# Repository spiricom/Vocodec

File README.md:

# Vocodec repository
Repository of code for the Snyderphonics Vocodec vocal processor unit.
requires LEAF as a submodule.

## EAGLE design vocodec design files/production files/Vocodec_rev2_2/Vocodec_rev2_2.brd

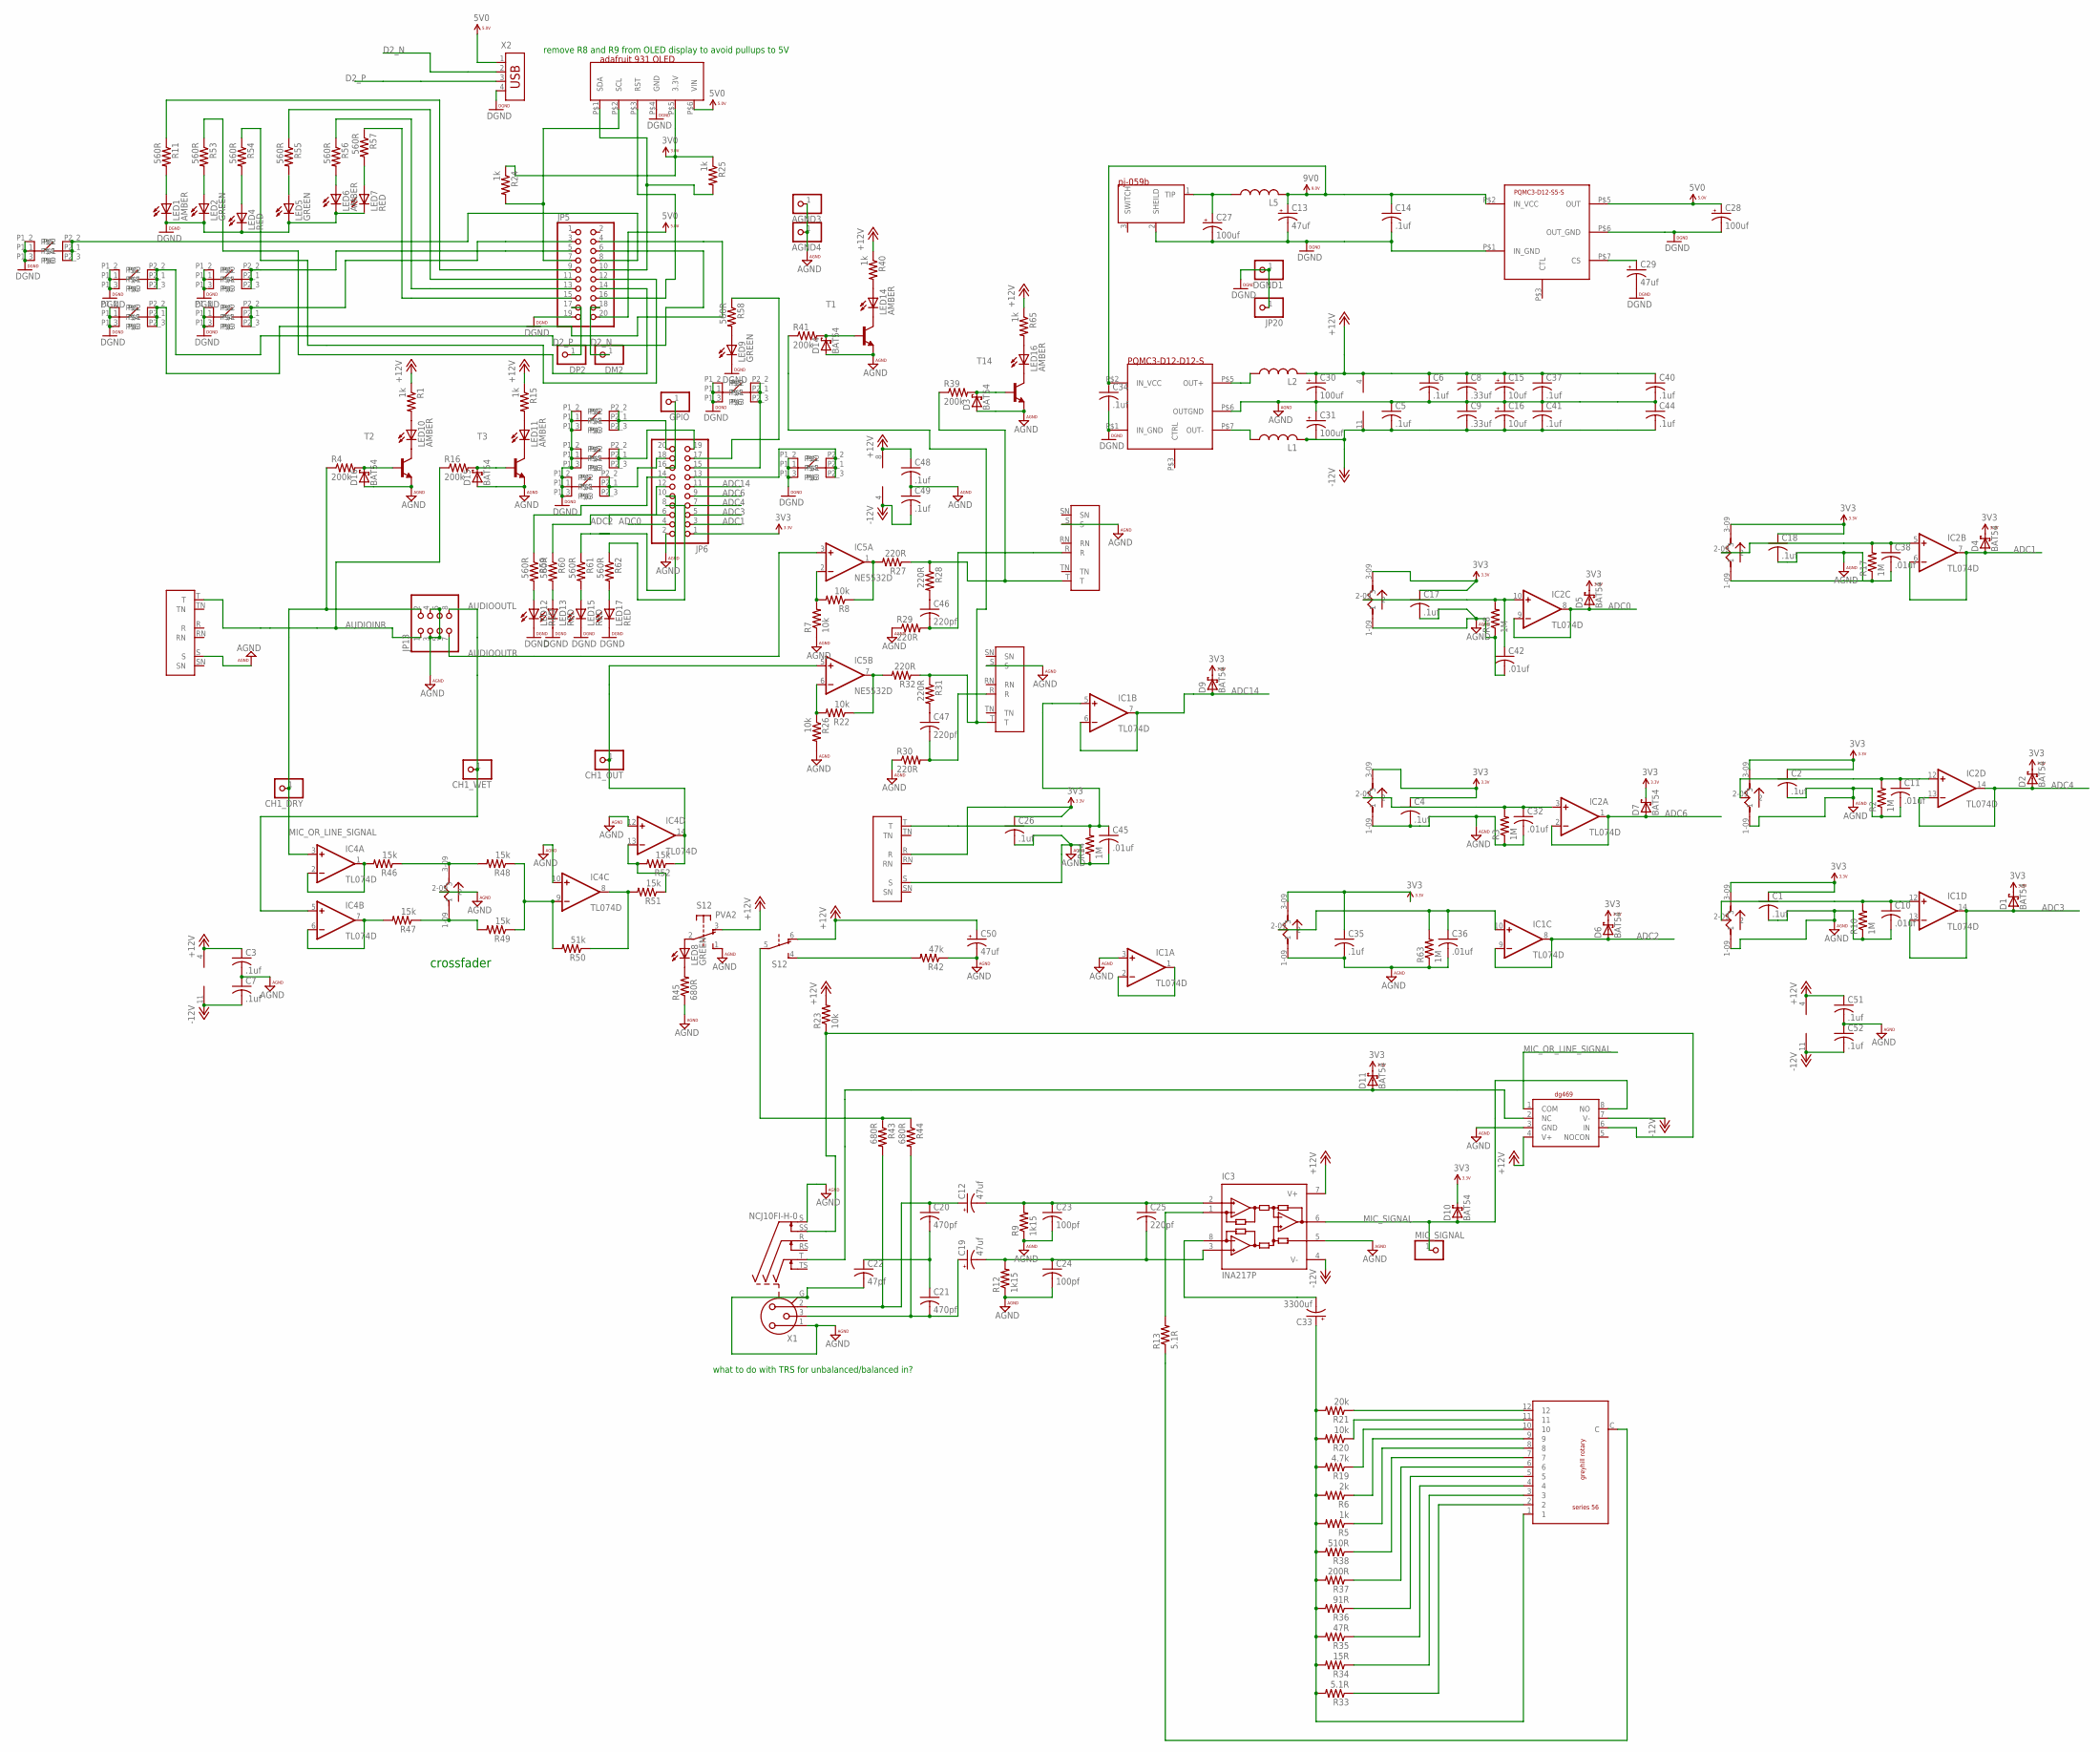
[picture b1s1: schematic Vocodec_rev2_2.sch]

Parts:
AGND3, AGND4: PINHD-1X1; 1X01; PARTNO *DNP
C1, C2, C3, C4, C5, C6, C7, C14, C17, C18, C26, C34, C35, C37, C40, C41, C44, C48, C49, C51, C52: .1uf; C0603; PARTNO CC0603KRX7R8BB104
C8, C9: .33uf; C0603; PARTNO C1608X7R1H334K080AC
C10, C11, C32, C36, C38, C42, C45: .01uf; C0603; PARTNO CC0603KRX7R8BB103
C12, C13, C19, C29, C50: 47uf; PANASONIC_E; PARTNO EEE-1VA470AP
C15, C16: 10uf; PANASONIC_C; PARTNO EEE-1VA100AR
C20, C21: 470pf; C0603; PARTNO CC0603JRNPO9BN471
C22: 47pf; C0603; PARTNO C0603C470J5GACTU
C23, C24: 100pf; C0603; PARTNO C0603C101J3GACTU
C25, C46, C47: 220pf; C0603; PARTNO CC0603JRNPO9BN221
C27, C28, C30, C31: 100uf; PANASONIC_F; PARTNO EEE-1EA101P
C33: 3300uf; E5-13; PARTNO EEU-FR1A332
CH1_DRY, CH1_OUT, CH1_WET: PINHD-1X1; 1X01; PARTNO *DNP
D1, D2, D3, D4, D5, D6, D7, D9, D10, D11, D14, D15, D16: BAT54; SOT23; PARTNO BAT54
DGND1: PINHD-1X1; 1X01; PARTNO *DNP
DM2: PINHD-1X1; 1X01; PARTNO *DNP
DP2: PINHD-1X1; 1X01; PARTNO *DNP
GPIO: PINHD-1X1; 1X01; PARTNO *DNP
IC1, IC2, IC4: TL074D; SO14; PARTNO TL074CDR
IC3: INA217P; DIL08; PARTNO *DNP
IC5: NE5532D; SO08; PARTNO NE5532DR
IC11: PQMC3-D12-D12-S; PARTNO PQMC3-D12-D12-S
IC12: PQMC3-D12-S5-S; PQMC3-D12-D12-S; PARTNO PQMC3-D12-S5-S
IC13: DG469; SO8; PARTNO DG469EY-T1-E3
J1, J3, J4, J9: NRJ6HF2; PARTNO NRJ6HF
J10: PJ-059B; PARTNO PJ-059A
JP5, JP6: PINHD-2X10; 2X10; PARTNO PRPC010DAAN-RC
JP13: PINHD-2X4; 2X04; PARTNO PRPC004DAAN-RC
JP20: PINHD-1X1; 1X01; PARTNO *DNP
L1, L2, L5: L-US6000-XXX-RC; 6000-XXXX-RC; PARTNO RLB9012-100KL
LED1, LED6, LED10, LED11, LED14, LED16: AMBER; PLCC2; PARTNO HSMU-A100-S00J1
LED2, LED5, LED8, LED9: GREEN; PLCC2; PARTNO HSMM-A101-R00J1
LED4, LED7, LED12, LED13, LED15, LED17: RED; PLCC2; PARTNO HSMZ-A100-R00J1
MIC_SIGNAL: PINHD-1X1; 1X01; PARTNO *DNP
OLED1: ADAFRUIT_931_OLED_128X32; ADAFRUIT_128X32_OLED; PARTNO *DNP
R1, R5, R15, R24, R25, R40, R65: 1k; R0603; PARTNO ESR03EZPF1001
R2, R3, R10, R14, R17, R18, R63: 1M; R0603; PARTNO CRCW06031M00FKEAHP
R4, R16, R39, R41: 200k; R0603; PARTNO ESR03EZPJ204
R6: 2k; R0603; PARTNO ERJ-PA3F2001V
R7, R8, R20, R22, R23, R26: 10k; R0603; PARTNO ESR03EZPF1002
R9, R12: 1k15; R0603; PARTNO ERA-3AEB1151V
R11, R53, R54, R55, R56, R57, R58, R59, R60, R61, R62: 560R; R0603; PARTNO ESR03EZPF5600
R13, R33: 5.1R; R0603; PARTNO RC0603JR-075R1L
R19: 4.7k; R0603; PARTNO CRCW06034K70FKEAHP
R21: 20k; R0603; PARTNO ESR03EZPF2002
R27, R28, R29, R30, R31, R32: 220R; R0603; PARTNO ESR03EZPJ221
R34: 15R; R0603; PARTNO RC0603JR-0715RL
R35: 47R; R0603; PARTNO RC0603JR-0747RL
R36: 91R; R0603; PARTNO RC0603JR-0791RL
R37: 200R; R0603; PARTNO RC0603JR-07200RL
R38: 510R; R0603; PARTNO RC0603JR-07510RL
R42: 47k; R0603; PARTNO ESR03EZPJ473
R43, R44, R45: 680R; R0603; PARTNO CRCW0603680RJNEAHP
R46, R47, R48, R49, R51, R52: 15k; R0603; PARTNO ESR03EZPF1502
R50: 51k; R0603; PARTNO ERJ-PA3F5102V
S12: PVA2; PVA2F; PARTNO PVA2 OA H4 1.7N V2
T1, T2, T3, T14: MMBT3904LT1-NPN-SOT23-BEC; SOT23-BEC; PARTNO MMBT3904-TP
U$1: 56DP30; PARTNO 56DP30-01-1-AJN
U$7, U$11, U$33, U$39, U$40, U$42, U$43, U$44, U$45, U$48: TL52_PLUS; PARTNO *DNP
U$12, U$14, U$16, U$27, U$28, U$31, U$32: RK09; PARTNO *DNP
X1: NCJ10FI-H-0; PARTNO NCJ10FI-H-01
X2: USB-787616; USB; PARTNO 292303-1

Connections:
3V0: OLED1.P$5 (3.3V), R24.1, R25.1
3V3: C1.1, C2.1, C4.1, C17.1, C18.1, C26.1, C35.1, D1.3 (C), D2.3 (C), D4.3 (C), D5.3 (C), D6.3 (C), D7.3 (C), D9.3 (C), D10.3 (C), D11.3 (C), J9.R, JP6.1, U$12.3-09 (3), U$16.3-09 (3), U$27.3-09 (3), U$28.3-09 (3), U$31.3-09 (3), U$32.3-09 (3)
5V0: C28.+, IC12.P$5 (OUT), JP5.20, OLED1.P$6 (VIN), X2.1
9V0: C13.+, C14.1, C34.1, IC11.P$2 (IN_VCC), IC12.P$2 (IN_VCC), L5.2
+12V: C3.1, C6.1, C8.1, C15.+, C30.+, C37.1, C40.1, C48.1, C50.+, C51.1, IC1.4 (V+), IC2.4 (V+), IC3.7 (V+), IC4.4 (V+), IC5.8 (V+), IC13.4 (V+), L2.2, R1.1, R15.1, R23.2, R40.1, R65.1, S12.3 (O), S12.6 (O)
-12V: C5.2, C7.2, C9.2, C16.-, C31.-, C41.2, C44.2, C49.2, C52.2, IC1.11 (V-), IC2.11 (V-), IC3.4 (V-), IC4.11 (V-), IC5.4 (V-), IC13.7 (V-), L1.2
ADC0: D5.1 (A), IC2.8 (OUT), IC2.9 (-IN), JP6.4
ADC1: D4.1 (A), IC2.6 (-IN), IC2.7 (OUT), JP6.3
ADC2: D6.1 (A), IC1.8 (OUT), IC1.9 (-IN), JP6.6
ADC3: D1.1 (A), IC1.13 (-IN), IC1.14 (OUT), JP6.5
ADC4: D2.1 (A), IC2.13 (-IN), IC2.14 (OUT), JP6.7
ADC6: D7.1 (A), IC2.1 (OUT), IC2.2 (-IN), JP6.9
ADC14: D9.1 (A), IC1.6 (-IN), IC1.7 (OUT), JP6.11
AGND: AGND3.1, AGND4.1, C1.2, C2.2, C3.2, C4.2, C5.1, C6.2, C7.1, C8.2, C9.1, C10.2, C11.2, C15.-, C16.+, C17.2, C18.2, C22.2, C23.2, C24.2, C26.2, C30.-, C31.+, C32.2, C35.2, C36.2, C37.2, C38.2, C40.2, C41.1, C42.2, C44.1, C45.2, C48.2, C49.1, C50.-, C51.2, C52.1, D3.1 (A), D14.1 (A), D15.1 (A), D16.1 (A), IC1.3 (+IN), IC3.5 (REF), IC4.10 (+IN), IC4.12 (+IN), IC11.P$6 (OUTGND), IC13.3 (GND), J1.S, J3.S, J4.S, J9.S, JP6.2, JP13.3, JP13.4, JP13.5, JP13.6, R2.1, R3.1, R7.1, R9.1, R10.1, R12.1, R14.1, R17.1, R18.1, R26.2, R29.1, R30.1, R42.1, R45.1, R63.1, S12.1 (S), T1.E, T2.E, T3.E, T14.E, U$12.1-09 (1), U$14.2-09 (2), U$16.1-09 (1), U$27.1-09 (1), U$28.1-09 (1), U$31.1-09 (1), U$32.1-09 (1), X1.1, X1.G, X1.S
AUDIOINR: J1.T, JP13.1, R16.1
AUDIOOUTL: CH1_WET.1, IC4.5 (+IN), JP13.8
AUDIOOUTR: IC5.3 (+IN), JP13.7
D2_N: DM2.1, JP5.18, X2.2
D2_P: DP2.1, JP5.17, X2.3
DGND: C13.-, C14.2, C27.-, C28.-, C29.-, C34.2, DGND1.1, IC11.P$1 (IN_GND), IC12.P$1 (IN_GND), IC12.P$6 (OUT_GND), J10.2 (SHEILD), JP5.19, JP20.1, LED1.C, LED2.C, LED4.C, LED5.C, LED6.C, LED7.C, LED9.C, LED12.C, LED13.C, LED15.C, LED17.C, OLED1.P$4 (GND), U$7.P1_1, U$7.P1_2, U$7.P1_3, U$11.P1_1, U$11.P1_2, U$11.P1_3, U$33.P1_1, U$33.P1_2, U$33.P1_3, U$39.P1_1, U$39.P1_2, U$39.P1_3, U$40.P1_1, U$40.P1_2, U$40.P1_3, U$42.P1_1, U$42.P1_2, U$42.P1_3, U$43.P1_1, U$43.P1_2, U$43.P1_3, U$44.P1_1, U$44.P1_2, U$44.P1_3, U$45.P1_1, U$45.P1_2, U$45.P1_3, U$48.P1_1, U$48.P1_2, U$48.P1_3, X2.4
MIC_OR_LINE_SIGNAL: CH1_DRY.1, IC4.3 (+IN), IC13.1 (COM), JP13.2, R4.1
MIC_SIGNAL: D10.1 (A), IC3.6 (OUT), IC13.8 (NO), MIC_SIGNAL.1
unnamed: IC5.2 (-IN), R7.2, R8.2
unnamed: IC5.6 (-IN), R22.2, R26.1
unnamed: LED10.C, T2.C
unnamed: IC5.1 (OUT), R8.1, R27.2
unnamed: LED10.A, R1.2
unnamed: IC1.1 (OUT), IC1.2 (-IN)
unnamed: LED11.C, T3.C
unnamed: D16.3 (C), R4.2, T2.B
unnamed: IC5.7 (OUT), R22.1, R32.2
unnamed: IC13.6 (IN), R23.1, X1.SS
unnamed: LED11.A, R15.2
unnamed: C33.+, R5.2, R6.2, R19.2, R20.2, R21.2, R33.2, R34.2, R35.2, R36.2, R37.2, R38.2, U$1.1
unnamed: D15.3 (C), R16.2, T3.B
unnamed: IC11.P$5 (OUT+), L2.1
unnamed: IC11.P$7 (OUT-), L1.1
unnamed: LED14.C, T1.C
unnamed: LED14.A, R40.2
unnamed: JP6.19, U$45.P2_1, U$45.P2_2, U$45.P2_3
unnamed: R21.1, U$1.12
unnamed: R20.1, U$1.11
unnamed: C12.-, C23.1, C25.1, IC3.2 (-IN), R9.2
unnamed: C19.+, C21.2, R44.2, X1.3
unnamed: C12.+, C20.1, R43.2, X1.2
unnamed: C20.2, C21.1, C22.1
unnamed: LED16.C, T14.C
unnamed: LED16.A, R65.2
unnamed: R19.1, U$1.10
unnamed: R6.1, U$1.9
unnamed: C19.-, C24.1, C25.2, IC3.3 (+IN), R12.2
unnamed: LED8.A, S12.2
unnamed: IC3.1 (RG1), R13.2
unnamed: D11.1 (A), IC13.2 (NC), X1.T
unnamed: R5.1, U$1.8
unnamed: R38.1, U$1.7
unnamed: R13.1, U$1.C
unnamed: R37.1, U$1.6
unnamed: R36.1, U$1.5
unnamed: R35.1, U$1.4
unnamed: R34.1, U$1.3
unnamed: R33.1, U$1.2
unnamed: J3.T, R27.1, R28.1, R39.1
unnamed: C46.2, J3.R, R29.2
unnamed: R42.2, S12.4 (S)
unnamed: C47.2, J4.R, R30.2
unnamed: D3.3 (C), R39.2, T14.B
unnamed: C46.1, R28.2
unnamed: C47.1, R31.2
unnamed: J4.T, R31.1, R32.1, R41.1
unnamed: LED8.C, R45.2
unnamed: C27.+, J10.1 (TIP), L5.1
unnamed: IC4.1 (OUT), IC4.2 (-IN), R46.2
unnamed: D14.3 (C), R41.2, T1.B
unnamed: C29.+, IC12.P$7 (CS)
unnamed: R43.1, R44.1, S12.5
unnamed: IC4.6 (-IN), IC4.7 (OUT), R47.2
unnamed: R46.1, R48.2, U$14.3-09 (3)
unnamed: C36.1, IC1.10 (+IN), R63.2, U$16.2-09 (2)
unnamed: IC4.8 (OUT), R50.1, R51.2
unnamed: IC4.9 (-IN), R48.1, R49.1, R50.2
unnamed: IC4.13 (-IN), R51.1, R52.2
unnamed: LED1.A, R11.2
unnamed: LED2.A, R53.2
unnamed: CH1_OUT.1, IC4.14 (OUT), IC5.5 (+IN), R52.1
unnamed: LED4.A, R54.2
unnamed: LED5.A, R55.2
unnamed: JP6.18, U$48.P2_1, U$48.P2_2, U$48.P2_3
unnamed: C33.-, IC3.8 (RG2)
unnamed: LED9.A, R58.2
unnamed: JP6.17, R58.1
unnamed: LED6.A, R56.2
unnamed: LED7.A, R57.2
unnamed: JP6.15, U$43.P2_1, U$43.P2_2, U$43.P2_3
unnamed: JP6.13, U$42.P2_1, U$42.P2_2, U$42.P2_3
unnamed: LED12.A, R59.2
unnamed: LED13.A, R60.2
unnamed: JP6.20, U$44.P2_1, U$44.P2_2, U$44.P2_3
unnamed: LED15.A, R61.2
unnamed: LED17.A, R62.2
unnamed: JP6.14, R59.1
unnamed: JP6.12, R60.1
unnamed: JP6.10, R61.1
unnamed: JP6.8, R62.1
unnamed: GPIO.1, JP6.16
unnamed: R47.1, R49.2, U$14.1-09 (1)
PA8: JP5.13, R56.1
PA9: JP5.16, OLED1.P$3 (RST)
PA10: JP5.15, R57.1
PB12: JP5.4, U$39.P2_1, U$39.P2_2, U$39.P2_3
PB13: JP5.3, U$7.P2_1, U$7.P2_2, U$7.P2_3
PB14: JP5.6, U$33.P2_1, U$33.P2_2, U$33.P2_3
PB15: JP5.5, U$11.P2_1, U$11.P2_2, U$11.P2_3
PC6: JP5.9, R11.1
PC7: JP5.12, R54.1
PC8: JP5.11, R55.1
PC9: JP5.14, R53.1
PD11_NOTIMER: JP5.8, U$40.P2_1, U$40.P2_2, U$40.P2_3
POT1: C10.1, IC1.12 (+IN), R10.2, U$12.2-09 (2)
POT3: C32.1, IC2.3 (+IN), R3.2, U$32.2-09 (2)
POT4: C11.1, IC2.12 (+IN), R2.2, U$31.2-09 (2)
POT7: C38.1, IC2.5 (+IN), R17.2, U$28.2-09 (2)
POT8: C42.1, IC2.10 (+IN), R18.2, U$27.2-09 (2)
POT9: C45.1, IC1.5 (+IN), J9.T, R14.2
SCL: JP5.7, OLED1.P$2 (SCL), R24.2
SDA: JP5.10, OLED1.P$1 (SDA), R25.2

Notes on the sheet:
remove R8 and R9 from OLED display to avoid pullups to 5V
crossfader
what to do with TRS for unbalanced/balanced in?

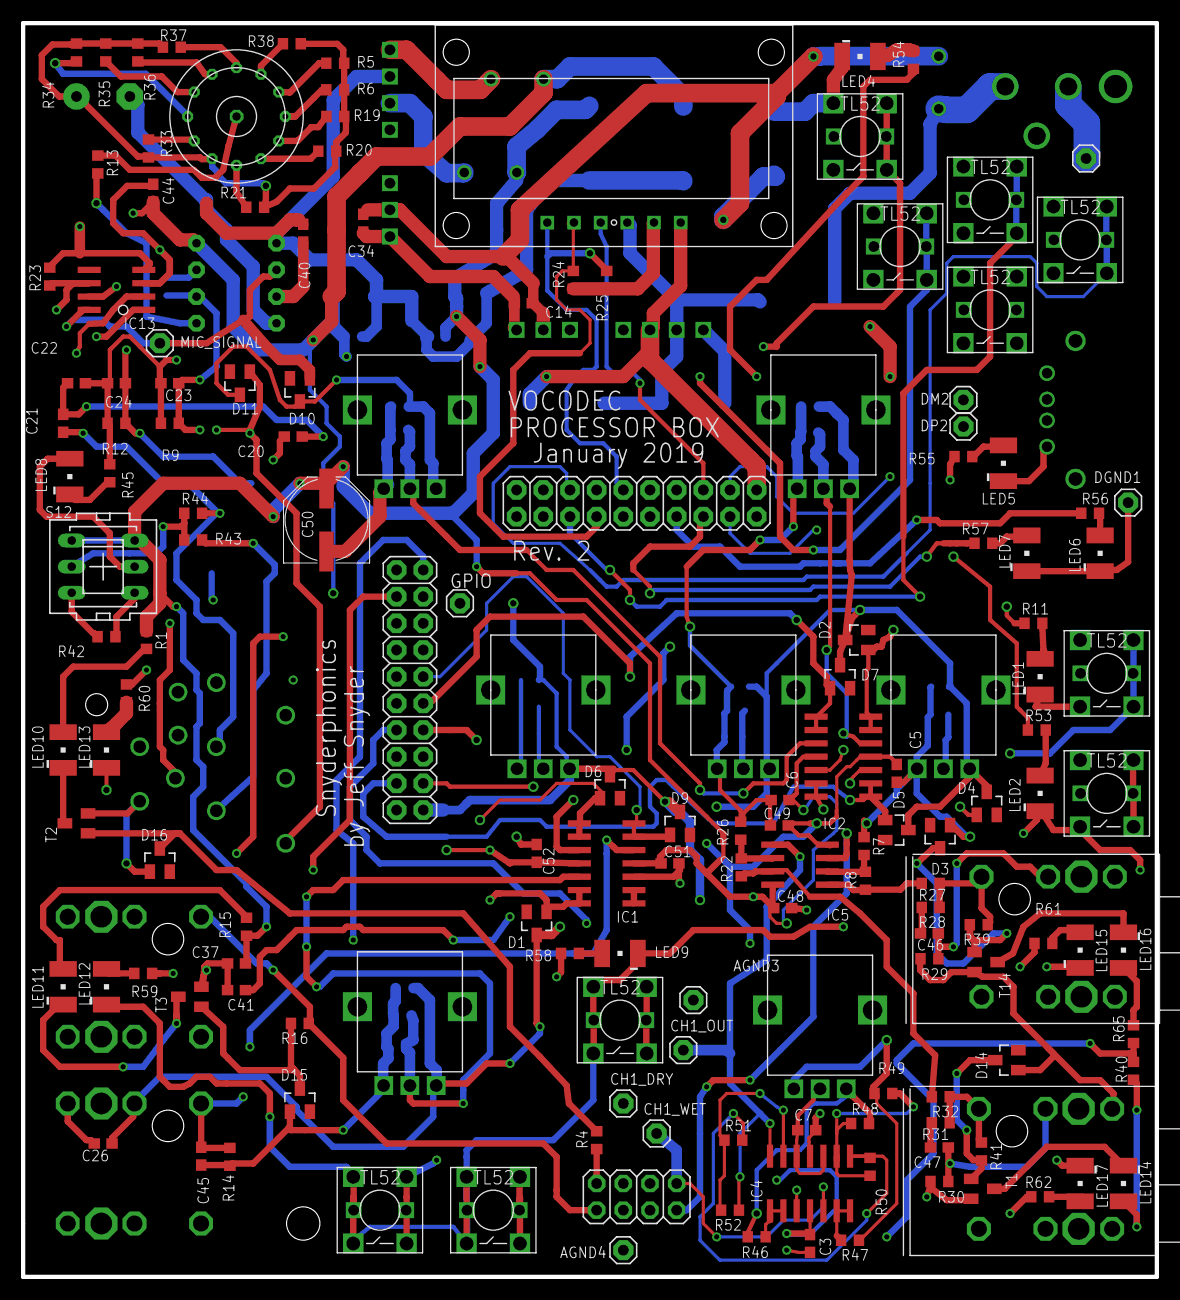
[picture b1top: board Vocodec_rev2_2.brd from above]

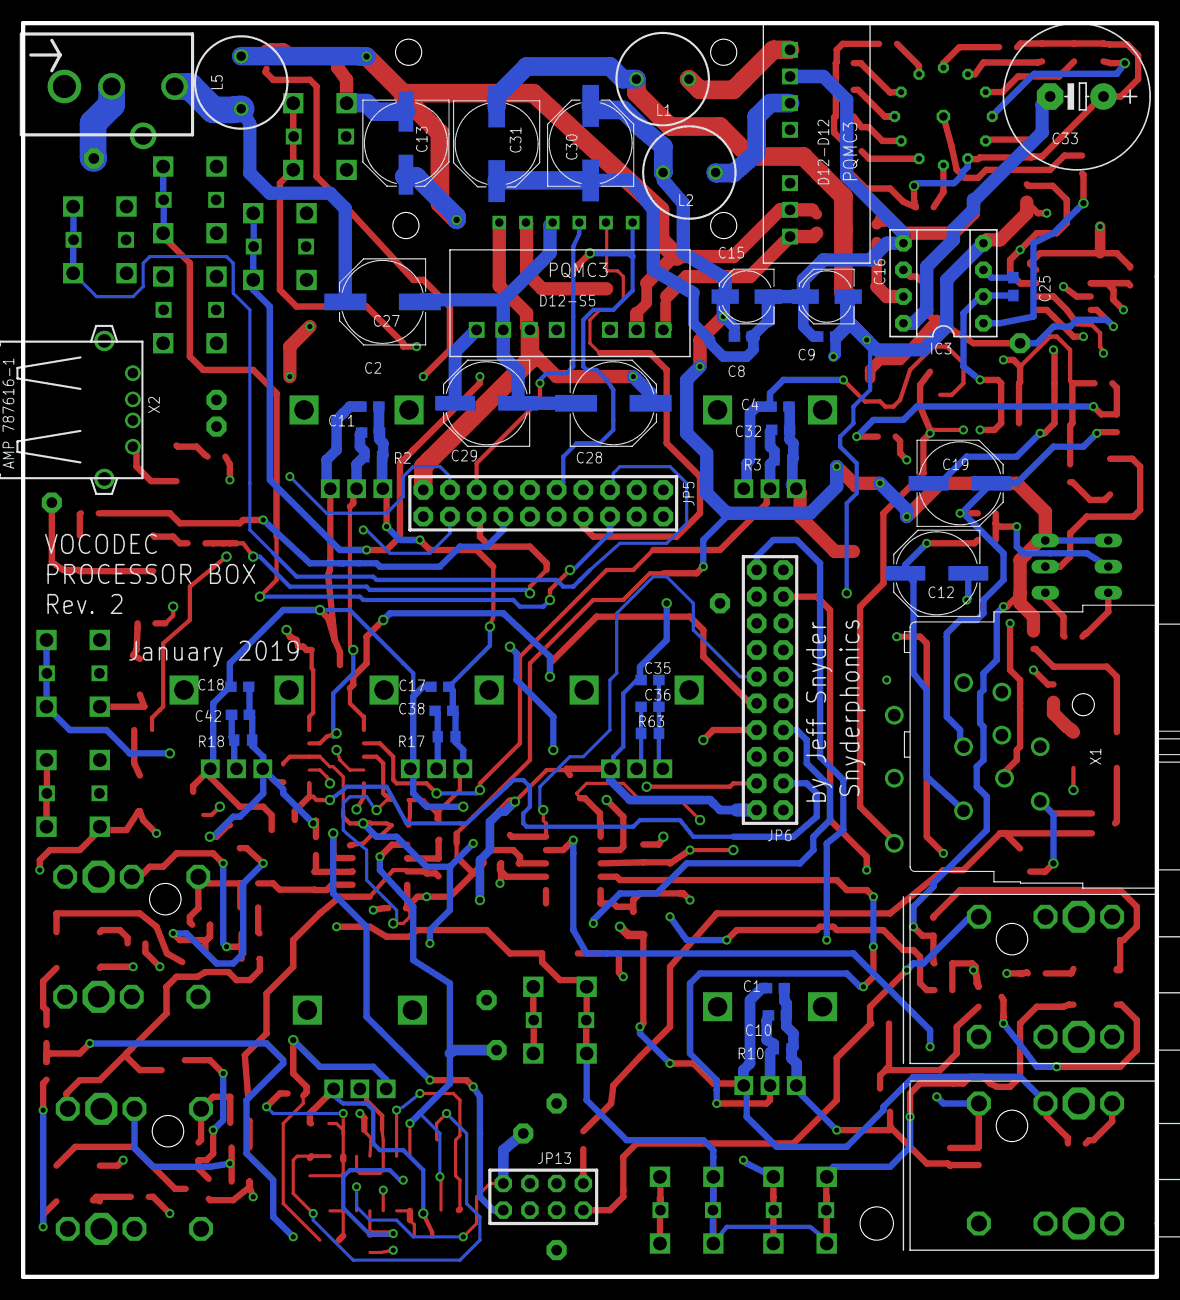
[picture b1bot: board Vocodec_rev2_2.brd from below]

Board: 4 copper layers, 108.0 x 119.4 mm, 199 parts (43 on the bottom side), 126 nets.

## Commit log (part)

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2020-01-25 played around with Living String preset and tuned parameters of pitchshifter
2020-01-26 testing formant shifter fixes
2020-01-26 working vocodec, got pitchshift with formant sounding decent.
2020-02-05 structure for handling button UI
2020-02-07 reorganizing ui and oled; developing the button ui structure; added some button text to neartune
2020-02-10 add basic button text for current presets; separate OLED_draw from OLED_process and move OLED_process into the audio loop (at the frame), this allows us to make ensure the display is in sync with the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
2020-02-11 add continuous hold button action; show record length when recordings a sample
2020-02-11 experimenting with waveform display on edit button
2020-02-14 move key control to edit+c
2020-02-14 add missing button and knob text
2020-02-17 consolidate preset and cv pedal assignment on edit hold + knob
2020-02-18 fix to knob val display when quickly changing value
2020-02-18 retune fix to snap to nearest midi note value rather than freq/period
2020-02-18 cleaning up button ui
2020-02-18 minor
2020-02-18 add edit screen
2020-02-19 adjust edit screen; replace sampler clear with sampler stop/play
2020-02-19 adjust sampler play/stop behavior and ui
2020-02-20 add fidelity threshold to first knob of neartune and autotune (moved amount and speed to knobs 2 and 3)
2020-02-21 did stuff
2020-02-23 added string synth and simple classic synth presets
2020-02-26 trying to fix cproject file
2020-02-26 Reverting to the state of the git commit 5b0a6a7085d6f49be0b834fa9321803058a30872
2020-02-26 update sfx ui and audiostream to pre revert
2020-02-27 add default preset values that won't change until knobs are turned; fix transitions clicks/glitches between presets; various minor ui fixes
2020-02-27 don't save knob values on preset change
2020-02-28 added fm rhodes synth
2020-03-01 new DX7 fm rhodes, also fixed oscillator to go through-zero.
2020-03-01 fixed issues with tPoly and note on off handling, and added pitch bend functionality. Still need to update other synth patches and vocoder synthesis patch to make use of new functionality
2020-03-01 improved rhodes sound
2020-03-02 added 4 different rhodes sub-presets, much better sounds
2020-03-02 improved classic synth preset;
2020-03-02 minor fixes for plork rehearsal
2020-03-07 starting a new branch for JairRohm
2020-03-18 Classic synth fixes and add missing knob name; rename Rhodes knobs TREM AMOUNT (was too long) to TREM DEPTH and TREM SPEED to TREM RATE
2020-04-17 keyboard sampler preset
2020-04-17 adjusting keyboard sampler behavior
2020-04-24 set LED controls
2020-04-28 finalized wavefolder to avoid glitches
2020-04-29 keyboard sampler improvements
2020-04-29 keyboard sampler poly usage fix
2020-05-04 classic synth adsr knob page
2020-05-05 trying some hysteresis options on the autotune, not sure how effective yet / what values are good
2020-05-05 synth fixes
2020-05-06 minor adjustments across presets
2020-05-06 added vocoder lpc warping
2020-05-06 added hex and elf to gitignore
2020-05-06 labeled controls
2020-05-06 fixed vocoder free function
2020-05-07 added Channel Vocoder preset - added noise source option to LPC vocoder
2020-05-07 restructured knob handling for easier multi-page presets
2020-05-07 setKnobValue function; cv pedal replaces knob instead of add
2020-05-07 setKnobValue(s) fix
2020-05-08 channel vocoder edits - added 2nd order vz filters
2020-05-08 fixed free function of channel vocoder
2020-05-08 improved channel vocoder
2020-05-12 messing with midi stuff to try to avoid stuck notes, not finished
2020-05-16 messing around with USB settings, still gets stuck notes sometimes
2020-05-17 still messed up usb but better
2020-05-17 working with impact keyboard, no toggle errors, but interrupting audio since priority is high
2020-05-18 works on impact keyboard but not on akai mpk - akai has toggle error repeated packet issue still sometimes. arghggggg
2020-05-18 working on nektar but not with mpk mini 2. Still unsure why usb host functionality does not work on akai
2020-05-19 got midi working well - went back to Xavier Haglund midi code and added what I learned into the hcd code - like masking off the NAK interrupts. still broken using an akai mpk2 but ive given up on that
2020-05-19 updated rhodes to use new sine wave and classic synth to use new saw
2020-05-21 now uses new adsrs
2020-05-21 edited GFX library trying to get descenders to work but didnt get it working. But I added cool cycle counter stuff functions in main, and redesigned the USB midi handling to do what Matt and I discus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
2020-05-21 changed some compiler optimizations, added -fno-strict-aliasing -fwrapv -Ofast and both section checkboxes, seems faster
2020-05-23 very nice rhodes sound working. there is now a cycle counter in the audio frame. Comment out the averaging of cycle counts when building for actual performance, it takes up a lot of time and can caus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
2020-05-23 got exponential buffer generation working, its excellent with the adsr timings. now need to also update LEAF
2020-05-26 removed cycle counter averaging in audioframe buffer
2020-05-26 limit number of midi messages that will be processed in a frame; clear on allocation for synths
2020-05-26 some rhodes changes
2020-05-26 removed params array and changed num osc per voice to 3 instead of 8 for classic synth
2020-05-27 worked on rhodes and classic synth so that release envelopes arent cut off when new notes come in - due to the poly not knowing they were busy. Added a state to poly indicating note off but also wait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
2020-05-27 added adsr for filter and glottal pulse to classic synth. Too much processing for glottal pulse but the adsr filter works great
2020-05-28 use alternating buffers for autosampler and add length/rate randomness to second page; fix classic synth mem leak
2020-05-29 much improved channel vocoder implementation
2020-06-01 reverb adjustments
2020-06-02 memory leak fixes
2020-06-02 lowered autosampler envelope follower threshold
2020-06-02 added pitchshift keyboard and fixed autosampler edge cases
2020-06-02 pitch quantization to overtone series for autosampler random speed
2020-06-03 improved living string implementation
2020-06-03 autosampler updates, now it stops recording buffer and starts playback when sample countdown is finished
2020-06-03 removed unused code in autosampler
2020-06-04 add ability to set living string freqs with midi input, decay/fb living string toggle; autosampler pitch quantization applies to speed knob
2020-06-05 fixed up autosampler to not click anymore. It was allowing the sample that just started recording to also still be playing back in the crossfade. Needed to check that the fade had finished. Also chan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
2020-06-05 just fixed broken free function in autosampler
2020-06-06 improved vocodec channel style, using tExpSmooth in place of tRamps and making the frame a little less heavy
2020-06-06 working on vocoder to avoid clicks
2020-06-07 many subtle fixes and overhaul of autotuneMono
2020-06-08 overhauled keyboard sampler. Now has gain smoothing to avoid clicks, and a button to make the knobs apply to all sounding voices.
2020-06-08 incorporating new leaf changes
2020-06-08 tTalkbox float version and more
2020-06-08 fixed noteOn issue
2020-06-08 cool changes to living string sympathetic preset
2020-06-09 much improved living string synth
2020-06-09 minor; string1 button text and string2 default adjustments
2020-06-09 string changes
2020-06-11 cleaned up free and alloc functions and got channel vocoder working without glitches again --- put it in the small pool and reduced some tick caluclations
2020-06-13 final vocodec firmware sent to beta testers
2020-06-13 updated leaf for vocodec
2020-06-17 replace freeFromPool calls with free
2020-06-17 fixed blank strings in ui
2020-06-24 make files compatible for juce use
2020-07-19 edits to tSampler
2020-07-19 updated code to use STM32CubeIDE instead of SW4STM32"
2020-07-20 fixed stm32cubeide version new linker file
2020-07-20 updated with Matts c extern code for JUCE compatibility of sfx and ui
2020-07-21 fixed usb interrupt issue
2020-07-21 actually fixed issue now, problem was the hal usb and hcd c and h files still allowed nack interrupts
2020-07-21 changed default mempool to small and removed that assume optimization flag because it caused issues with the string synth patch
2020-07-21 fixed some little float issues, etc
2020-07-21 switched a lot of uint8_t variables to int to avoid extra masking instructions when working with non natural types on 32bit platform;
2020-07-21 add readd Debug folder .gitignore
2020-07-21 getting rid of some warnings
2020-07-21 add more files to Debug gitignore
2020-07-21 testing push, changed tanh in vocoder2 to be LEAF_tanh
2020-07-21 testing push
2020-07-21 changed tanh in vocoder2 to be an approximation to improve performance with many notes at once. Some subtle changes to keyboard sampler as well
2020-08-19 fixed clear on allocation and initializing freq array to avoid slowness on string synth before notes are pressed
2020-08-20 minor updates for leaf changes and use in plugin version
2020-08-25 plugin compatibility changes
2020-08-26 plugin compatibility updates
2020-08-26 use long long for pgm_read_dword for portability
2020-09-27 updated to take new leaf structure with no globals into account
2020-11-13 building but can't program chip
2020-11-13 fixed elf
2020-11-17 new pitchshifter and vocodec code except screen working
2020-11-17 oled buffer fix; fix initialization order
2020-12-19 trying out experiments with different strings models
2020-12-20 cool version using tExpLivingString for experimentation
2021-03-02 integrated latest changes to JUCE plugin
2021-06-29 wavetable removal from hardware;
2022-09-25 updated with current CubeIDE
2025-01-16 saving before trying preset saving procedure
2025-10-04 working but audio not tested, about to switch to new leaf
2025-11-11 working with rev4 genera brain
2025-11-29 working but USB fails enumeration
2025-11-29 version with broken leaf but trying to fix usb issues
2025-11-29 messing around with usb stuff, not working
2025-11-30 new version works on rev4 board with USB fixed
2025-11-30 about to try new smoothers
2025-12-01 improved knob smoothing by adding andy simper dynamic smoother. also changed frame size to 64 which works for all except pitch shifters, which need some optimizing to not have occasional overruns. pu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
2025-12-01 fixed tape delay preset
2026-06-04 working vocodec improved tape delay, shipping to Lea
2026-06-11 shipped to lea
2026-06-12 simplified version, has most vocodec stuff removed, adds simple sine wave, usb midi control works, no sd card yet
2026-06-13 doesnt build, currently about to add updated filesystem stuff
2026-06-13 now can read preset names off of sd card
2026-06-13 working sd card, loads preset. now working on getting midi back
2026-06-13 working with loading preset from sd card and using midi keyboard to control it. still cant do proper monophonic handling or use knobs or buttons or display
2026-06-13 got the knob input working
2026-06-14 working, now need to make the display show preset names
2026-06-16 good working version, now with pitch bend, working display, stable. next I will try to get usart midi in working
2026-06-16 version before testing on experimenter
2026-06-16 vocodec on experimenter, fixed mistake in loading preset, removed oled for now. still has two knobs incorrect and the buttons and leds are wrong. but works!
2026-06-18 display is working, next going to work on uart midiinput
2026-06-19 knob fix
2026-06-19 knob behavior better, and working on getting uart integrated for midi input
2026-06-19 commented
2026-06-19 receiving midi via uart

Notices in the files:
parts and their libraries:
SparkFun-Connectors: Licensing: Creative Commons ShareAlike 4.0 International - https://creativecommons.org/licenses/by-sa/4.0
PatternAgents-Beautify: License : http://creativecommons.org/licenses/by-sa/3.0
(Creative Commons 3.0)
